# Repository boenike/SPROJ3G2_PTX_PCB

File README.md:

# SPROJ3G2_PTX_PCB
SPROJ3EEG2 PTX PCB - KiCad files

Author: Bence Tóth

Course: BEng in Electronics

Campus: SDU Sonderborg

Semester: 3rd

Finish date: 2024/12/23

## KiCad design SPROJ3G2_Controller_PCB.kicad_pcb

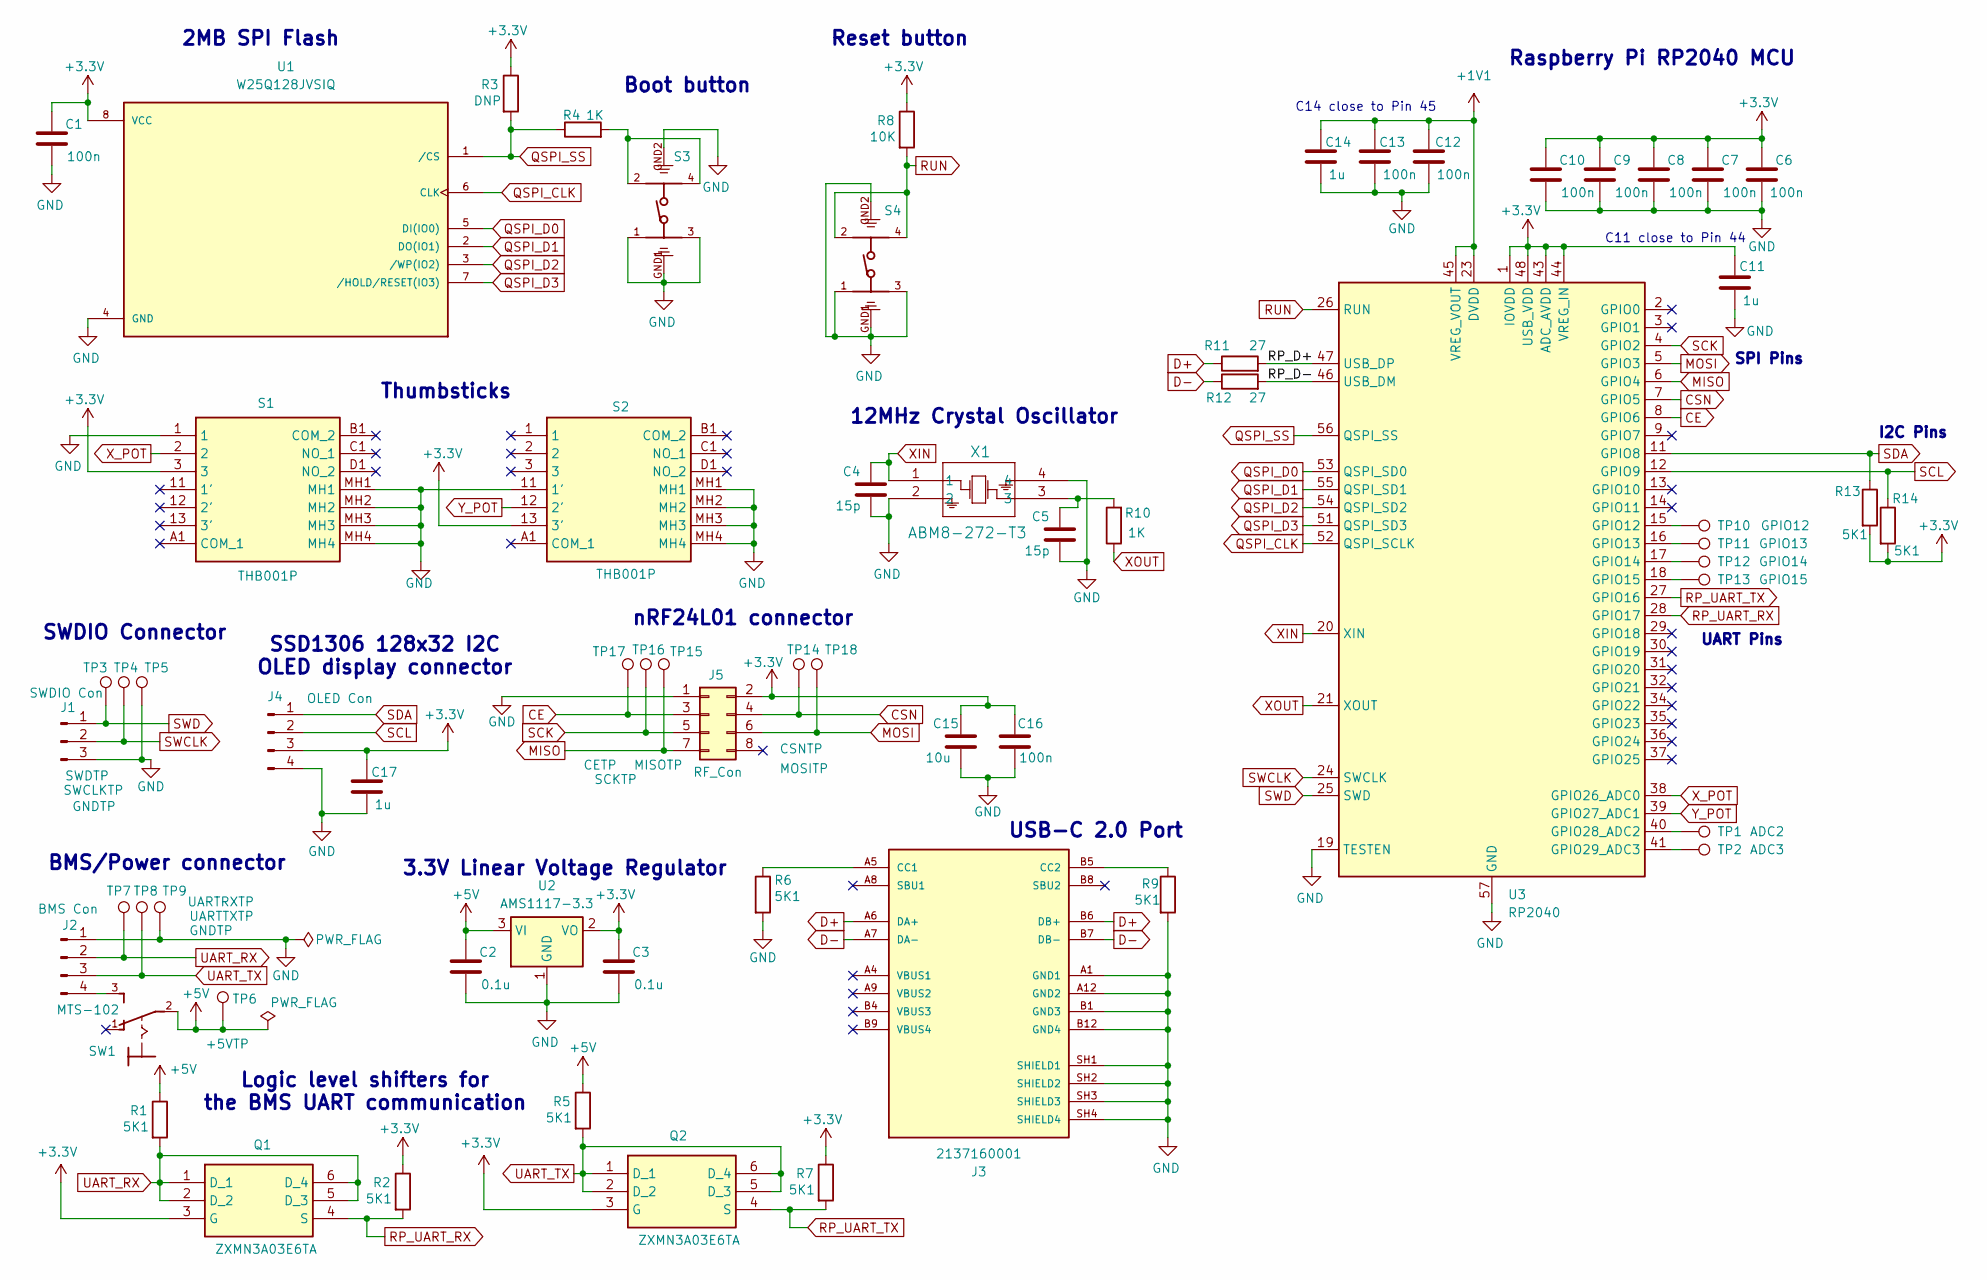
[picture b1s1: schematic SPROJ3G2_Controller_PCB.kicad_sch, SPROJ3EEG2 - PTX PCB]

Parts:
C1, C6, C7, C8, C9, C10, C12, C13, C16: 100n; C_0805_2012Metric
C2, C3: 0.1u; C_0805_2012Metric
C4, C5: 15p; C_0805_2012Metric
C11, C14, C17: 1u; C_0805_2012Metric
C15: 10u; C_0805_2012Metric
J1: SWDIO Con; JST_PH_S3B-PH-K_1x03_P2.00mm_Horizontal
J2: BMS Con; JST_PH_S4B-PH-K_1x04_P2.00mm_Horizontal
J3: 2137160001; PARTREV B
J4: OLED Con; PinHeader_1x04_P2.54mm_Vertical
J5: RF_Con; PinHeader_2x04_P2.54mm_Vertical
Q1, Q2: ZXMN3A03E6TA; Manufacturer_Part_Number ZXMN3A03E6TA; Mouser Part Number 522-ZXMN3A03E6TA
R1, R2, R5, R6, R7, R9, R13, R14: 5K1; R_0805_2012Metric
R3: DNP; R_0805_2012Metric
R4, R10: 1K; R_0805_2012Metric
R8: 10K; R_0805_2012Metric
R11, R12: 27; R_0805_2012Metric
S1, S2: THB001P; Manufacturer_Part_Number THB001P; Mouser Part Number 611-THB001P
S3, S4: 431183015816; PART-NUMBER 431183015816
SW1: MTS-102; Toggle_Switch_MTS-102
TP1: ADC2; TestPoint_Pad_D1.0mm
TP2: ADC3; TestPoint_Pad_D1.0mm
TP3: SWDTP; TestPoint_Pad_D1.0mm
TP4: SWCLKTP; TestPoint_Pad_D1.0mm
TP5, TP9: GNDTP; TestPoint_Pad_D1.0mm
TP6: +5VTP; TestPoint_Pad_D1.0mm
TP7: UARTRXTP; TestPoint_Pad_D1.0mm
TP8: UARTTXTP; TestPoint_Pad_D1.0mm
TP10: GPIO12; TestPoint_Pad_D1.0mm
TP11: GPIO13; TestPoint_Pad_D1.0mm
TP12: GPIO14; TestPoint_Pad_D1.0mm
TP13: GPIO15; TestPoint_Pad_D1.0mm
TP14: CSNTP; TestPoint_Pad_D1.0mm
TP15: MISOTP; TestPoint_Pad_D1.0mm
TP16: SCKTP; TestPoint_Pad_D1.0mm
TP17: CETP; TestPoint_Pad_D1.0mm
TP18: MOSITP; TestPoint_Pad_D1.0mm
U1: W25Q128JVSIQ; PARTREV I
U2: AMS1117-3.3; SOT-223-3_TabPin2
U3: RP2040; QFN-56-1EP_7x7mm_P0.4mm_EP3.2x3.2mm
X1: ABM8-272-T3; ABM8-272-T3_ABR

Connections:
+1V1: C12.1, C13.1, C14.1, U3.23 (DVDD), U3.45 (VREG_VOUT), U3.50 (DVDD)
+3.3V: C1.1, C3.1, C6.1, C7.1, C8.1, C9.1, C10.1, C11.1, C15.1, C16.1, C17.1, J4.3, J5.2, Q1.3 (G), Q2.3 (G), R2.1, R3.1, R7.1, R8.1, R13.2, R14.2, S1.3, S2.13 (3'), U1.8 (VCC), U2.2 (VO), U3.1 (IOVDD), U3.10 (IOVDD), U3.22 (IOVDD), U3.33 (IOVDD), U3.42 (IOVDD), U3.43 (ADC_AVDD), U3.44 (VREG_IN), U3.48 (USB_VDD), U3.49 (IOVDD)
+5V: C2.1, R1.1, R5.1, SW1.2, TP6.1, U2.3 (VI)
/RP_D+: R11.2, U3.47 (USB_DP)
/RP_D-: R12.2, U3.46 (USB_DM)
CE: J5.3, TP17.1, U3.8 (GPIO6)
CSN: J5.4, TP14.1, U3.7 (GPIO5)
D+: J3.A6 (DA+), J3.B6 (DB+), R11.1
D-: J3.A7 (DA-), J3.B7 (DB-), R12.1
GND: C1.2, C2.2, C3.2, C4.2, C5.2, C6.2, C7.2, C8.2, C9.2, C10.2, C11.2, C12.2, C13.2, C14.2, C15.2, C16.2, C17.2, J1.3, J2.1, J3.A1 (GND1), J3.A12 (GND2), J3.B1 (GND3), J3.B12 (GND4), J3.SH1 (SHIELD1), J3.SH2 (SHIELD2), J3.SH3 (SHIELD3), J3.SH4 (SHIELD4), J4.4, J5.1, R6.2, R9.2, S1.1, S1.MH1, S1.MH2, S1.MH3, S1.MH4, S2.11 (1'), S2.MH1, S2.MH2, S2.MH3, S2.MH4, S3.1, S3.3, S3.GND1, S3.GND2, S4.1, S4.3, S4.GND1, S4.GND2, TP5.1, TP9.1, U1.4 (GND), U2.1 (GND), U3.19 (TESTEN), U3.57 (GND), X1.2, X1.4
MISO: J5.7, TP15.1, U3.6 (GPIO4)
MOSI: J5.6, TP18.1, U3.5 (GPIO3)
unnamed: C5.1, R10.2, X1.3
unnamed: J2.4, SW1.3
unnamed: J3.A5 (CC1), R6.1
unnamed: J3.B5 (CC2), R9.1
unnamed: R4.2, S3.2, S3.4
unnamed: TP10.1, U3.15 (GPIO12)
unnamed: TP11.1, U3.16 (GPIO13)
unnamed: TP12.1, U3.17 (GPIO14)
unnamed: TP13.1, U3.18 (GPIO15)
unnamed: TP1.1, U3.40 (GPIO28_ADC2)
unnamed: TP2.1, U3.41 (GPIO29_ADC3)
QSPI_CLK: U1.6 (CLK), U3.52 (QSPI_SCLK)
QSPI_D0: U1.5 (DI(IO0)), U3.53 (QSPI_SD0)
QSPI_D1: U1.2 (DO(IO1)), U3.55 (QSPI_SD1)
QSPI_D2: U1.3 (/WP(IO2)), U3.54 (QSPI_SD2)
QSPI_D3: U1.7 (/HOLD/RESET(IO3)), U3.51 (QSPI_SD3)
QSPI_SS: R3.2, R4.1, U1.1 (/CS), U3.56 (QSPI_SS)
RP_UART_RX: Q1.4 (S), R2.2, U3.28 (GPIO17)
RP_UART_TX: Q2.4 (S), R7.2, U3.27 (GPIO16)
RUN: R8.2, S4.2, S4.4, U3.26 (RUN)
SCK: J5.5, TP16.1, U3.4 (GPIO2)
SCL: J4.2, R14.1, U3.12 (GPIO9)
SDA: J4.1, R13.1, U3.11 (GPIO8)
SWCLK: J1.2, TP4.1, U3.24 (SWCLK)
SWD: J1.1, TP3.1, U3.25 (SWD)
UART_RX: J2.2, Q1.1 (D_1), Q1.2 (D_2), Q1.5 (D_3), Q1.6 (D_4), R1.2, TP7.1
UART_TX: J2.3, Q2.1 (D_1), Q2.2 (D_2), Q2.5 (D_3), Q2.6 (D_4), R5.2, TP8.1
XIN: C4.1, U3.20 (XIN), X1.1
XOUT: R10.1, U3.21 (XOUT)
X_POT: S1.2, U3.38 (GPIO26_ADC0)
Y_POT: S2.12 (2'), U3.39 (GPIO27_ADC1)

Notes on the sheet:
SPI Pins
C11 close to Pin 44
Raspberry Pi RP2040 MCU
12MHz Crystal Oscillator
nRF24L01 connector
SSD1306 128x32 I2C OLED display connector
Boot button
USB-C 2.0 Port
Thumbsticks
Reset button
2MB SPI Flash
C14 close to Pin 45
SWDIO Connector
Logic level shifters for the BMS UART communication
3.3V Linear Voltage Regulator
BMS/Power connector
UART Pins
I2C Pins

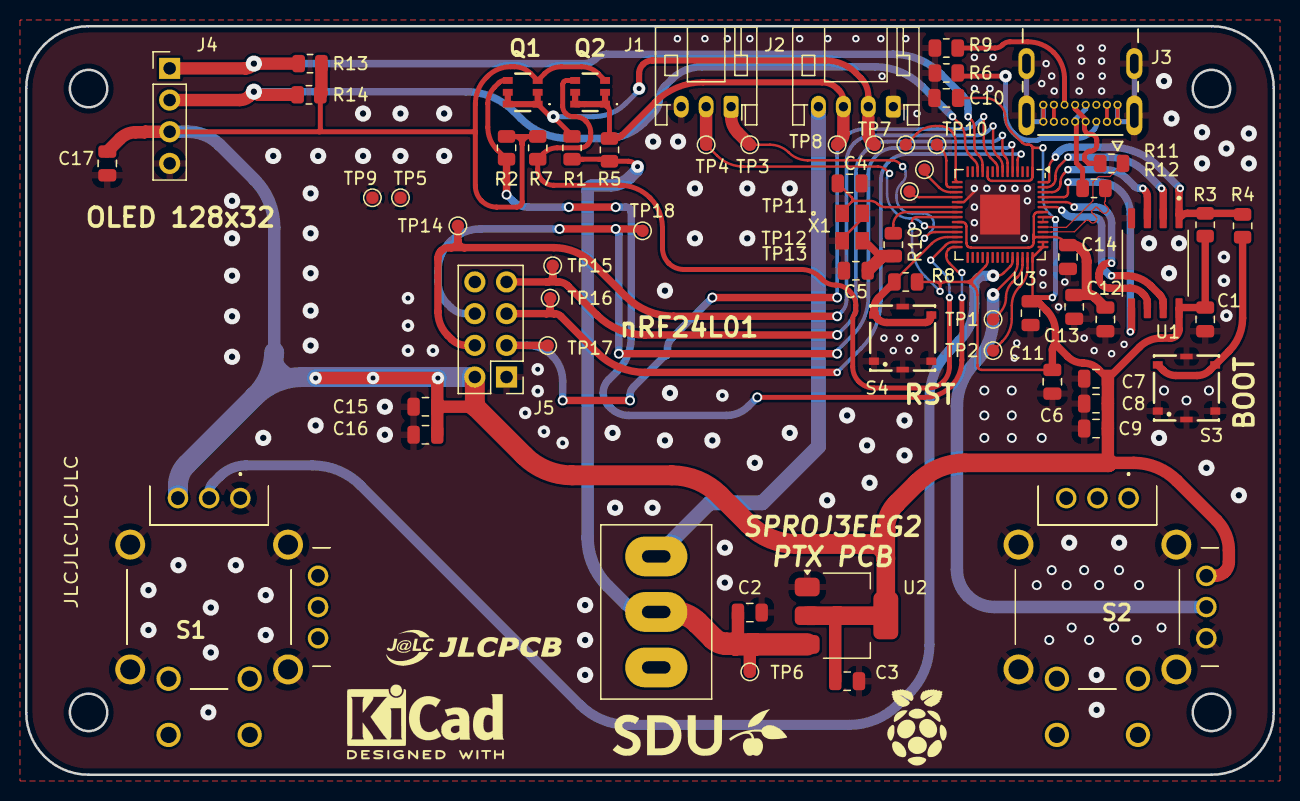
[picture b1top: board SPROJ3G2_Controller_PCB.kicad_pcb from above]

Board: 2 copper layers, 100.0 x 60.0 mm, 65 parts (0 on the bottom side), 43 nets.

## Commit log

2024-12-09 PCB files upload
    PCB files upload
2024-12-20 Schematic cleanup
    Schematic cleanup
2024-12-20 Clean-up
    Clean-up
